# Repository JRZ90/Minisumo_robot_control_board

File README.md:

## Minisumo robot control board
Custom control board for mini sumo robots with an ATmega 328 as the main controller, a TB6612 for motor control, connections for up to 5 analog or digital opponent sensors, 3 "dohyo" line sensors, 2 user buttons and a dip -switch for quick strategy configuration. This board can work with a 2 or 3 cell lipo battery.

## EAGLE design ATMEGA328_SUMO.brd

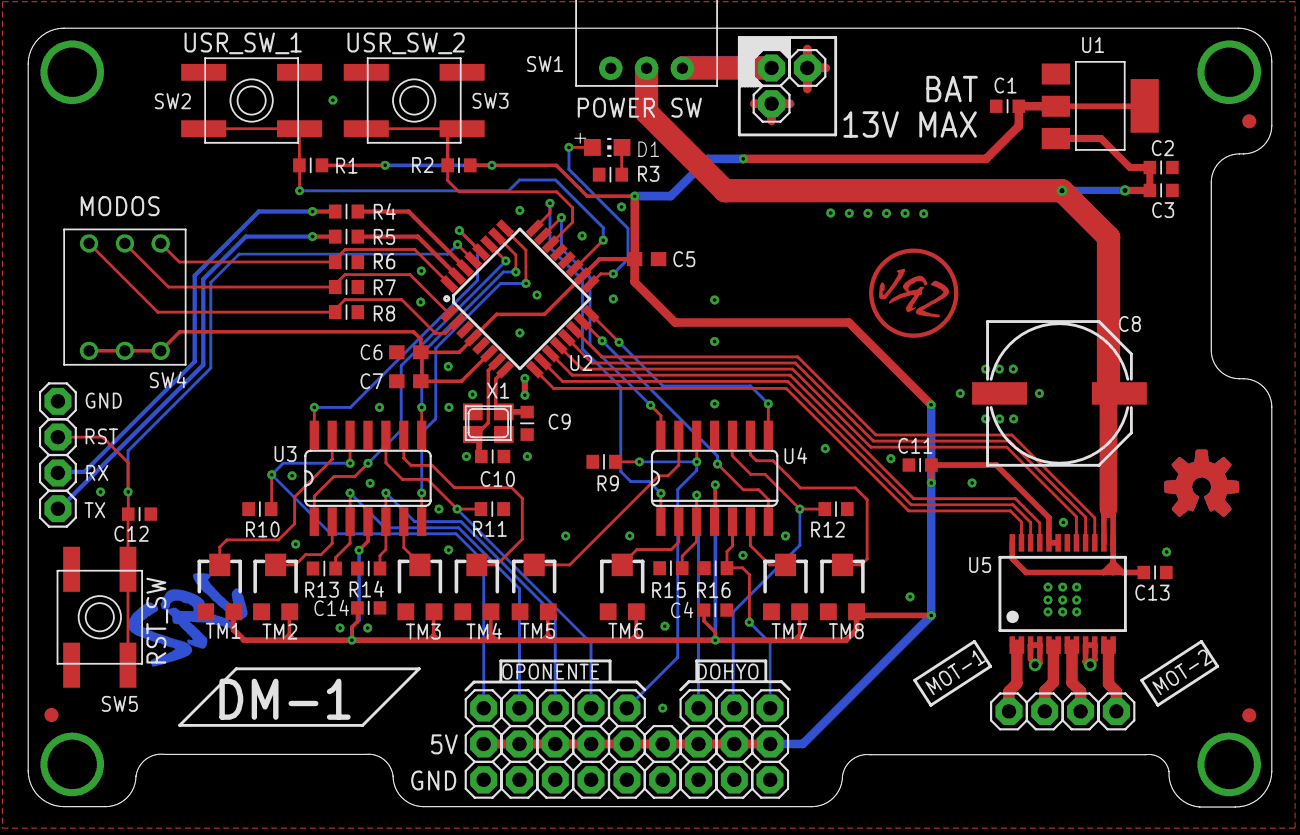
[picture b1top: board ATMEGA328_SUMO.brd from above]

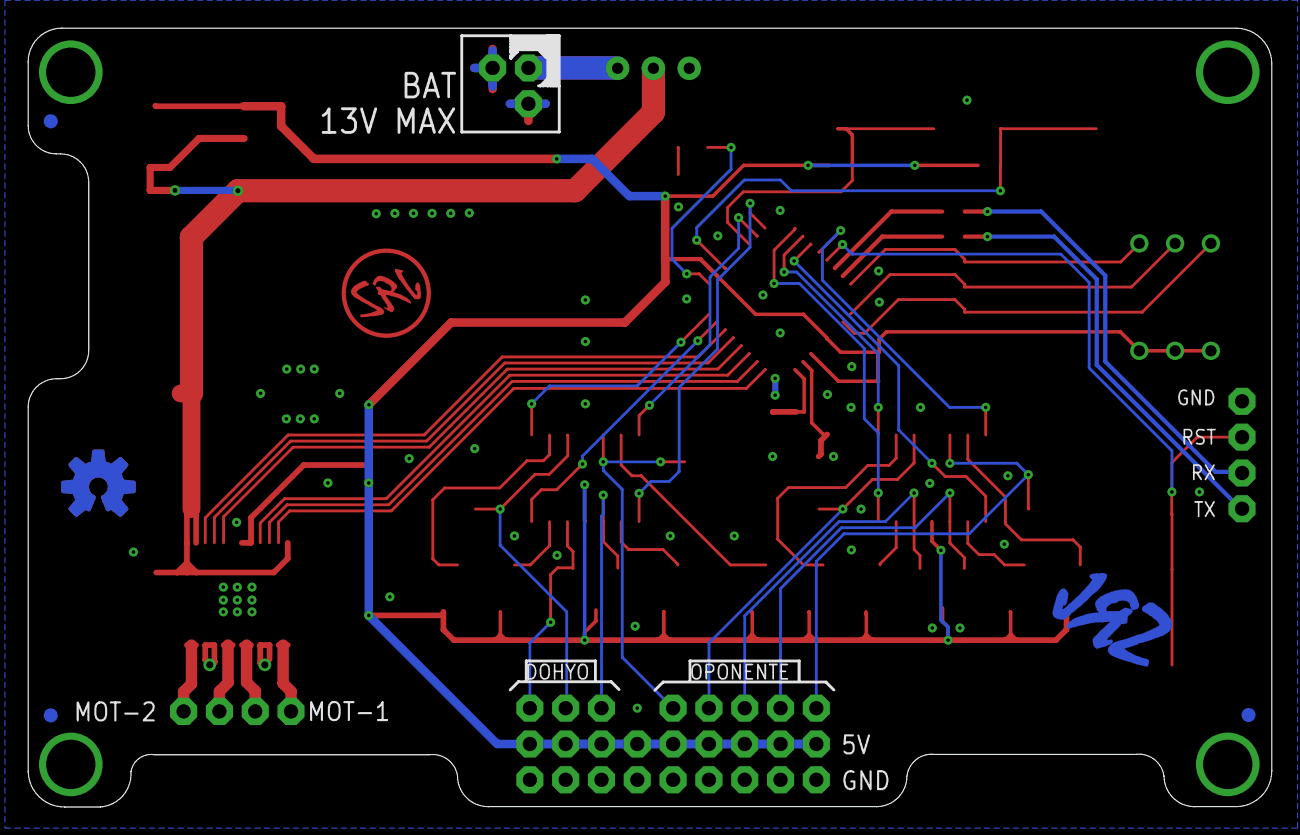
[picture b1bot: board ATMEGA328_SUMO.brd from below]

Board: 2 copper layers, 88.2 x 55.2 mm, 96 parts (4 on the bottom side), 52 nets.

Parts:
C1, C2: 4.7uF; CAPC1608X92N
C3, C4, C11, C12, C13, C14: 100nF; CAPC1608X92N
C5, C6, C7: 100nF; C0603
C8: 2200uF/16V; PANASONIC_G
C9, C10: 22pF; CAPC1608X92N
D1: CHIP-LED0805
JP1, JP2, JP3, JP4, JP5, JP6, JP7, JP8, JP9, JP10, JP11, JP12, JP13, JP14, JP15, JP16, JP17, JP18, JP19, JP20, JP21, JP22, JP23, JP24, JP25, JP26, JP27, JP28, JP29, JP30, JP31, JP32, JP33: 1X01
MOT-1A1, MOT-1A2, MOT-1B1, MOT-1B2: 1X01
R1: R4; RESC1608X55N
R2, R6, R7, R8, R9, R10, R11, R12, R13, R14, R15, R16: 10K; RESC1608X55N
R3: 330R; RESC1608X55N
R4, R5: 1K; RESC1608X55N
SW1: LCSC-C92657; 450302014072
SW2: LCSC_C318887; EVQ-Q2
SW3, SW5: SPST_TACT-EVQQ2__C318887; EVQ-Q2
SW4: LCSC-C52648; 418117170903
TM1, TM2, TM3, TM4, TM5, TM6, TM7, TM8: 10K; TC33X
U1: AMS1117-5.0__C6187; SOT-223
U2: ATMEGA328P_TQFP; TQFP32-08
U3, U4: LM324D; SO14
U5: TB6612FNG; SSOP24
U$1, U$3, U$4, U$100, U$101, U$102: FIDUCIAL; FIDUCIAL_1MM
U$2: LOGO_B
U$6, U$7: OSHWLOGO_TOP_0.2
X1: 16MHz; NX3225

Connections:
5V: C1.2, C4.1, C5.1, C6.1, C7.1, C11.1, C14.1, JP16.1, JP17.1, JP18.1, JP19.1, JP20.1, JP21.1, JP22.1, JP23.1, JP24.1, R1.2, R2.2, SW4.1, SW4.2, SW4.3, TM1.3, TM2.3, TM3.3, TM4.3, TM5.3, TM6.3, TM7.3, TM8.3, U1.2, U1.4, U2.4, U2.6, U2.18, U3.4, U4.4, U5.19, U5.20
BAT+: C2.2, C3.2, C8.+, C13.2, SW1.1, U1.3, U5.13, U5.14, U5.24
DS1: R6.1, SW4.4, U2.32
DS2: R7.1, SW4.5, U2.1
DS3: R8.1, SW4.6, U2.2
GND: C1.1, C2.1, C3.1, C4.2, C5.2, C6.2, C7.2, C8.-, C9.2, C10.2, C11.2, C12.2, C13.1, C14.2, JP2.1, JP3.1, JP4.1, JP25.1, JP26.1, JP27.1, JP28.1, JP29.1, JP30.1, JP31.1, JP32.1, JP33.1, R3.1, R6.2, R7.2, R8.2, R9.2, R10.1, R11.1, R12.1, R13.1, R14.1, R15.1, R16.1, SW2.A, SW2.A', SW3.A, SW3.A', SW5.B, SW5.B', TM1.1, TM2.1, TM3.1, TM4.1, TM5.1, TM6.1, TM7.1, TM8.1, U1.1, U2.3, U2.5, U2.21, U3.11, U4.11, U5.3, U5.4, U5.9, U5.10, U5.18, X1.2, X1.4
IN1_M1: U2.11, U5.21
IN1_M2: U2.12, U5.17
IN2_M1: U2.10, U5.22
IN2_M2: U2.13, U5.16
LED_PIN: D1.A, U2.17
unnamed: D1.C, R3.2
unnamed: JP10.1, R14.2, U3.5
unnamed: JP11.1, R11.2, U3.10
unnamed: TM2.2, U3.2
unnamed: TM3.2, U3.6
unnamed: TM4.2, U3.9
unnamed: MOT-1B2.1, U5.5, U5.6
unnamed: TM1.2, U3.13
unnamed: TM5.2, U4.13
unnamed: JP12.1, R9.1, U4.12
unnamed: TM6.2, U4.2
unnamed: JP8.1, R10.2, U3.12
unnamed: JP13.1, R15.2, U4.3
unnamed: JP9.1, R13.2, U3.3
unnamed: MOT-1B1.1, U5.1, U5.2
unnamed: C9.1, U2.8, X1.1
unnamed: C10.1, U2.7, X1.3
unnamed: MOT-1A2.1, U5.11, U5.12
unnamed: MOT-1A1.1, U5.7, U5.8
unnamed: TM7.2, U4.6
unnamed: JP15.1, R16.2, U4.5
unnamed: JP1.1, SW1.3
unnamed: TM8.2, U4.9
unnamed: JP14.1, R12.2, U4.10
PB3: U2.15, U4.7
PB4: U2.16, U4.8
PC0: U2.23, U4.14
PC1: U2.24, U4.1
PC2: U2.25, U3.7
PC3: U2.26, U3.8
PC4: U2.27, U3.1
PC5: U2.28, U3.14
PWM_M1: U2.9, U5.23
PWM_M2: U2.14, U5.15
RST: C12.1, JP5.1, SW5.A, SW5.A', U2.29
RX: JP6.1, R4.1
RX.: R4.2, U2.30
TX: JP7.1, R5.1
TX.: R5.2, U2.31
USR_SW1: R2.1, SW3.B, SW3.B', U2.22
USR_SW2: R1.1, SW2.B, SW2.B', U2.19

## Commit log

2021-05-25 primer commit, todo funciona pero falta terminar algunas cosas
2021-05-25 Segundo commit con todo listo para compartir
2021-05-26 correccion de algunos errores menores en DRC
2021-05-26 correccion de algunos herrores menores en ERC

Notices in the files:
parts and their libraries:
SparkFun-Passives: Licensing: Creative Commons ShareAlike 4.0 International - https://creativecommons.org/licenses/by-sa/4.0
Eagle_Wuerth_Elektronik_Switch_rev15b: Copyright: Würth Elektronik
